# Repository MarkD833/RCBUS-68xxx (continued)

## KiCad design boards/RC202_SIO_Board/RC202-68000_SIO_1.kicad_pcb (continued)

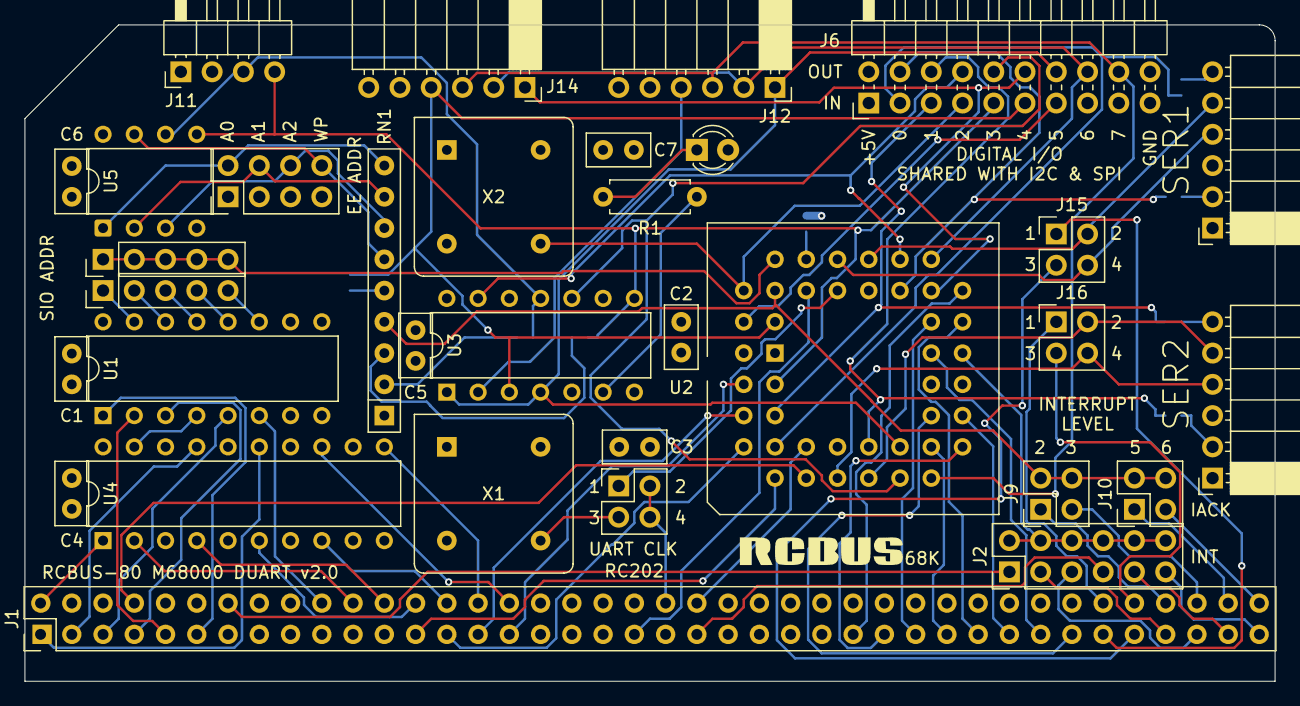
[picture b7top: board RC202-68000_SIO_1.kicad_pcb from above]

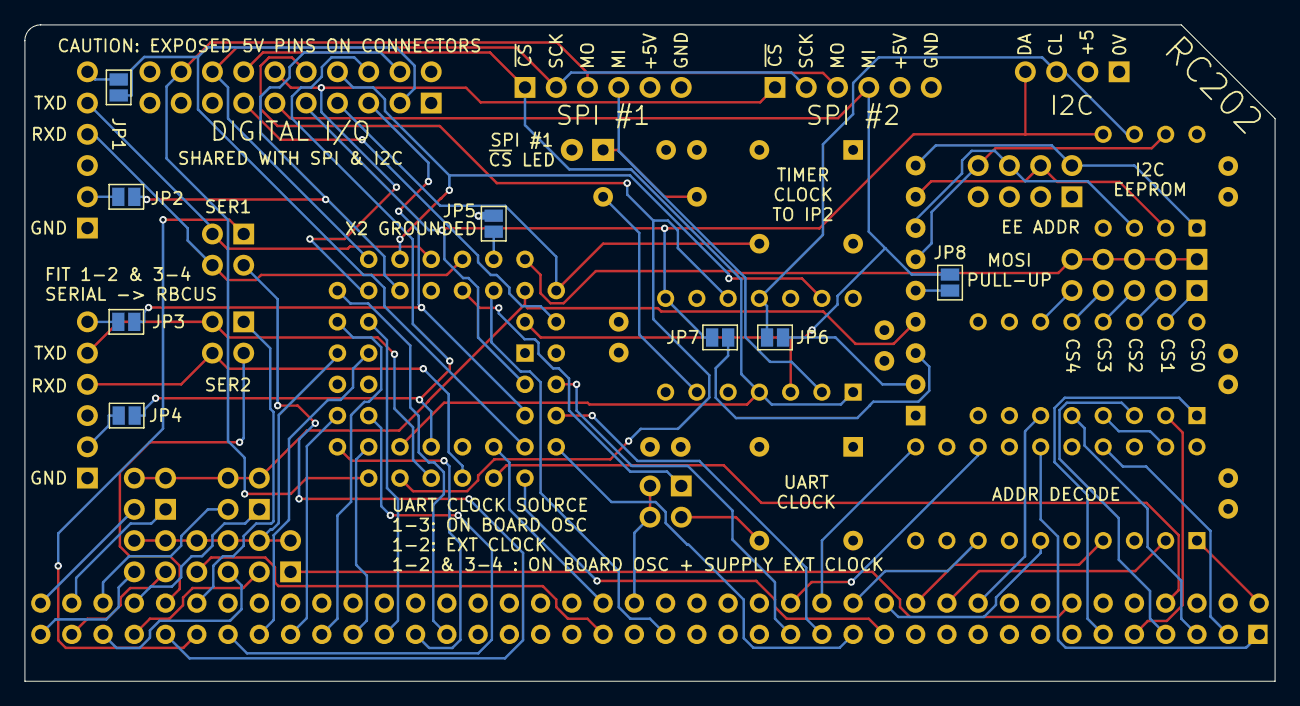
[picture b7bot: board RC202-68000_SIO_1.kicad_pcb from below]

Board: 4 copper layers, 101.6 x 53.3 mm, 41 parts (8 on the bottom side), 91 nets.

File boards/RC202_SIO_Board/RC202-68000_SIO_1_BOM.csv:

Reference,Value,Qty,Description
"C1,C2,C3,C4,C5,C6,C7",100n,7,Unpolarized ceramic capacitor
D1,LED,1,Light emitting diode
J1,RCBus_80PIN_68000,1,"Generic connector, double row, 02x40, right angle"
J2,Conn_02x06_Odd_Even,1,"Generic connector, double row, 02x06"
"J3,J4,J12,J14",Conn_01x06,4,"Generic connector, single row, 01x06, right angle"
"J5,J9,J10,J15,J16",Conn_02x02_Odd_Even,5,"Generic connector, double row, 02x02"
J6,Conn_02x10_Odd_Even,1,"Generic connector, double row, 02x10"
"J7,J8",Conn_01x05,2,"Generic connector, single row, 01x05"
J11,Conn_01x04,1,"Generic connector, single row, 01x04"
J13,Conn_02x04_Odd_Even,1,"Generic connector, double row, 02x04"
"JP1,JP2,JP3,JP4,JP6,JP7,JP8",SolderJumper,7,"Solder Jumper, 2-pole, open"
R1,1K,1,Resistor
RN1,4K7,1,"8 resistor network, star topology, bussed resistors, small symbol"
U1,74LS138,1,Decoder 3 to 8 active low outputs
U2,SCC68692C1A44,1,DUART + 8 Outputs & 6 Inputs
U3,74LS125,1,Quad buffer 3-State outputs
U4,74LS688,1,8-bit magnitude comparator
U5,24LC128,1,"I2C Serial EEPROM, 128Kb, DIP-8"
X1,3.6864MHz,1,"Crystal Clock Oscillator, DIP8-style metal package"
X2,1.0MHz,1,"Crystal Clock Oscillator, DIP8-style metal package"

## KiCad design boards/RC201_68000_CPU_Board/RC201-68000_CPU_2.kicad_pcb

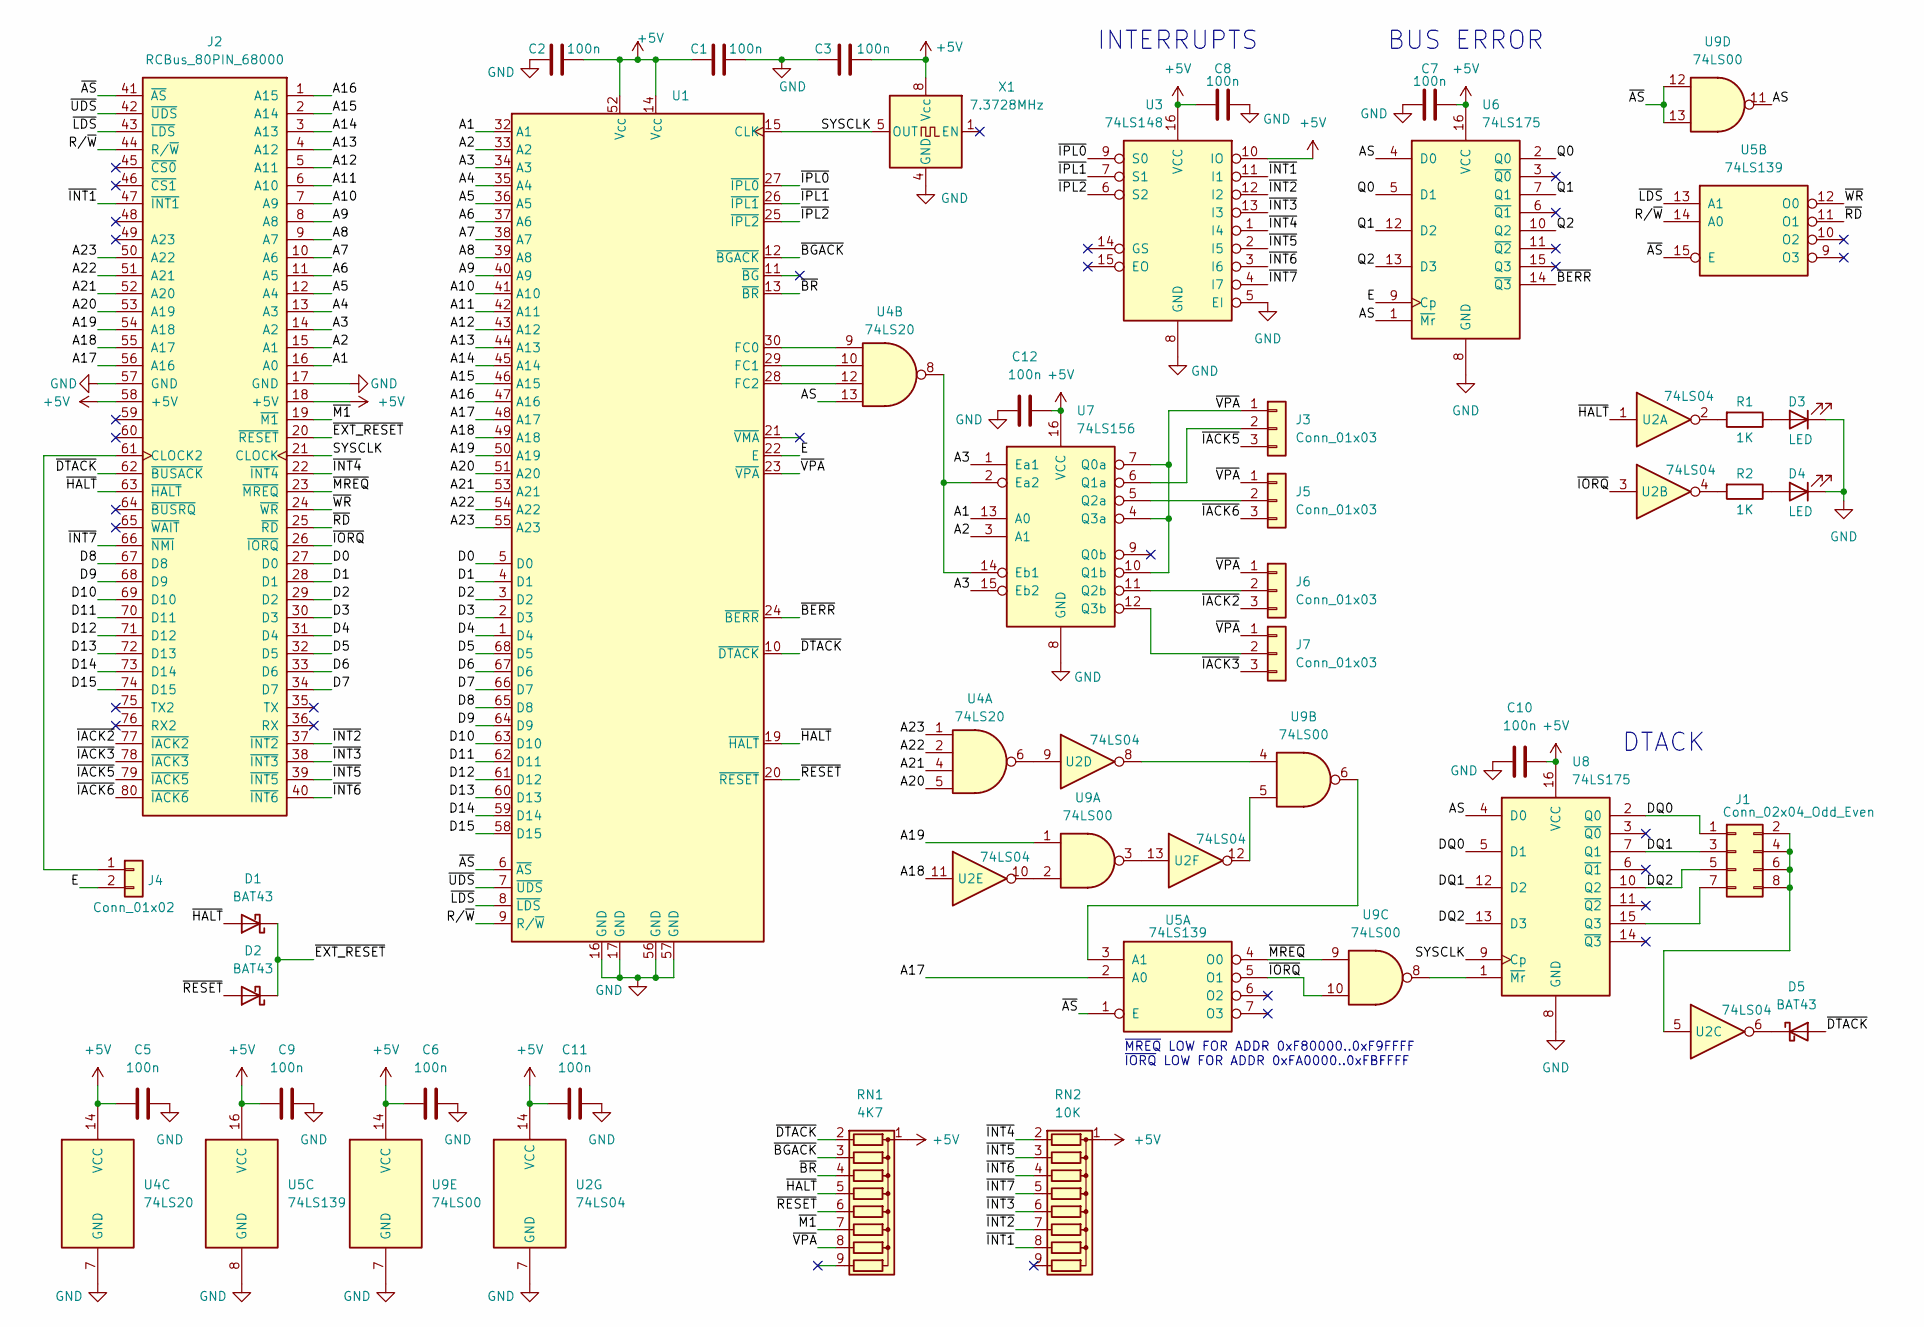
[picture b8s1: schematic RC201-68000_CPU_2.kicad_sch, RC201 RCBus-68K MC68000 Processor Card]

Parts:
C1, C2, C3, C5, C6, C7, C8, C9, C10, C11, C12: 100n; C_Disc_D5.0mm_W2.5mm_P2.50mm
D1, D2, D5: BAT43; D_DO-35_SOD27_P7.62mm_Horizontal
D3, D4: LED; LED_D3.0mm
J1: Conn_02x04_Odd_Even; PinHeader_2x04_P2.54mm_Vertical
J2: RCBus_80PIN_68000; RCBus_80p_Medium
J3, J5, J6, J7: Conn_01x03; PinHeader_1x03_P2.54mm_Vertical
J4: Conn_01x02; PinHeader_1x02_P2.54mm_Vertical
R1, R2: 1K; R_Axial_DIN0207_L6.3mm_D2.5mm_P7.62mm_Horizontal
RN1: 4K7; R_Array_SIP9
RN2: 10K; R_Array_SIP9
U1: PLCC-68_THT-Socket
U2: 74LS04; DIP-14_W7.62mm
U3: 74LS148; DIP-16_W7.62mm
U4: 74LS20; DIP-14_W7.62mm
U5: 74LS139; DIP-16_W7.62mm
U6, U8: 74LS175; DIP-16_W7.62mm
U7: 74LS156; DIP-16_W7.62mm
U9: 74LS00; DIP-14_W7.62mm
X1: 7.3728MHz; Oscillator_DIP-8

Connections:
+5V: C1.1, C2.2, C3.2, C5.1, C6.1, C7.2, C8.1, C9.1, C10.2, C11.1, C12.2, J2.18 (+5V), J2.58 (+5V), RN1.1 (common), RN2.1 (common), U1.14 (V_{CC}), U1.52 (V_{CC}), U2.14 (VCC), U3.10 (IO), U3.16 (VCC), U4.14 (VCC), U5.16 (VCC), U6.16 (VCC), U7.16 (VCC), U8.16 (VCC), U9.14 (VCC), X1.8 (Vcc)
/A1: J2.16 (A0), U1.32 (A1), U7.13 (A0)
/A2: J2.15 (A1), U1.33 (A2), U7.3 (A1)
/A3: J2.14 (A2), U1.34 (A3), U7.1 (Ea1), U7.15 (Eb2)
/A4: J2.13 (A3), U1.35 (A4)
/A5: J2.12 (A4), U1.36 (A5)
/A6: J2.11 (A5), U1.37 (A6)
/A7: J2.10 (A6), U1.38 (A7)
/A8: J2.9 (A7), U1.39 (A8)
/A9: J2.8 (A8), U1.40 (A9)
/A10: J2.7 (A9), U1.41 (A10)
/A11: J2.6 (A10), U1.42 (A11)
/A12: J2.5 (A11), U1.43 (A12)
/A13: J2.4 (A12), U1.44 (A13)
/A14: J2.3 (A13), U1.45 (A14)
/A15: J2.2 (A14), U1.46 (A15)
/A16: J2.1 (A15), U1.47 (A16)
/A17: J2.56 (A16), U1.48 (A17), U5.2 (A0)
/A18: J2.55 (A17), U1.49 (A18), U2.11
/A19: J2.54 (A18), U1.50 (A19), U9.1
/A20: J2.53 (A19), U1.51 (A20), U4.5
/A21: J2.52 (A20), U1.53 (A21), U4.4
/A22: J2.51 (A21), U1.54 (A22), U4.2
/A23: J2.50 (A22), U1.55 (A23), U4.1
/AS: U4.13, U6.1 (~Mr), U6.4 (D0), U8.4 (D0), U9.11
/D0: J2.27 (D0), U1.5 (D0)
/D1: J2.28 (D1), U1.4 (D1)
/D2: J2.29 (D2), U1.3 (D2)
/D3: J2.30 (D3), U1.2 (D3)
/D4: J2.31 (D4), U1.1 (D4)
/D5: J2.32 (D5), U1.68 (D5)
/D6: J2.33 (D6), U1.67 (D6)
/D7: J2.34 (D7), U1.66 (D7)
/D8: J2.67 (D8), U1.65 (D8)
/D9: J2.68 (D9), U1.64 (D9)
/D10: J2.69 (D10), U1.63 (D10)
/D11: J2.70 (D11), U1.62 (D11)
/D12: J2.71 (D12), U1.61 (D12)
/D13: J2.72 (D13), U1.60 (D13)
/D14: J2.73 (D14), U1.59 (D14)
/D15: J2.74 (D15), U1.58 (D15)
/DQ0: J1.1, U8.2 (Q0), U8.5 (D1)
/DQ1: J1.3, U8.7 (Q1), U8.12 (D2)
/DQ2: J1.5, U8.10 (Q2), U8.13 (D3)
/E: J4.2, U1.22 (E), U6.9 (Cp)
/Q0: U6.2 (Q0), U6.5 (D1)
/Q1: U6.7 (Q1), U6.12 (D2)
/Q2: U6.10 (Q2), U6.13 (D3)
/R/~W: J2.44 (R/~W), U1.9 (R/~W), U5.14 (A0)
/SYSCLK: J2.21 (CLOCK), U1.15 (CLK), U8.9 (Cp), X1.5 (OUT)
/~AS: J2.41 (~AS), U1.6 (~AS), U5.1 (E), U5.15 (E), U9.12, U9.13
/~BERR: U1.24 (~BERR), U6.14 (~Q3)
/~BGACK: RN1.3 (R2), U1.12 (~BGACK)
/~BR: RN1.4 (R3), U1.13 (~BR)
/~DTACK: D5.2 (A), J2.62 (~BUSACK), RN1.2 (R1), U1.10 (~DTACK)
/~EXT_RESET: D1.1 (K), D2.1 (K), J2.20 (~RESET)
/~HALT: D1.2 (A), J2.63 (~HALT), RN1.5 (R4), U1.19 (~HALT), U2.1
/~IACK2: J2.77 (~IACK2), J6.3
/~IACK3: J2.78 (~IACK3), J7.3
/~IACK5: J2.79 (~IACK5), J3.3
/~IACK6: J2.80 (~IACK6), J5.3
/~INT1: J2.47 (~INT1), RN2.8 (R7), U3.11 (I1)
/~INT2: J2.37 (~INT2), RN2.7 (R6), U3.12 (I2)
/~INT3: J2.38 (~INT3), RN2.6 (R5), U3.13 (I3)
/~INT4: J2.22 (~INT4), RN2.2 (R1), U3.1 (I4)
/~INT5: J2.39 (~INT5), RN2.3 (R2), U3.2 (I5)
/~INT6: J2.40 (~INT6), RN2.4 (R3), U3.3 (I6)
/~INT7: J2.66 (~NMI), RN2.5 (R4), U3.4 (I7)
/~IORQ: J2.26 (~IORQ), U2.3, U5.5 (O1), U9.10
/~IPL0: U1.27 (~IPL0), U3.9 (S0)
/~IPL1: U1.26 (~IPL1), U3.7 (S1)
/~IPL2: U1.25 (~IPL2), U3.6 (S2)
/~LDS: J2.43 (~LDS), U1.8 (~LDS), U5.13 (A1)
/~M1: J2.19 (~M1), RN1.7 (R6)
/~MREQ: J2.23 (~MREQ), U5.4 (O0), U9.9
/~RD: J2.25 (~RD), U5.11 (O1)
/~RESET: D2.2 (A), RN1.6 (R5), U1.20 (~RESET)
/~UDS: J2.42 (~UDS), U1.7 (~UDS)
/~VPA: J3.1, J5.1, J6.1, J7.1, RN1.8 (R7), U1.23 (~VPA), U7.4 (Q3a), U7.7 (Q0a), U7.10 (Q1b)
/~WR: J2.24 (~WR), U5.12 (O0)
GND: C1.2, C2.1, C3.1, C5.2, C6.2, C7.1, C8.2, C9.2, C10.1, C11.2, C12.1, D3.1 (K), D4.1 (K), J2.17 (GND), J2.57 (GND), U1.16 (GND), U1.17 (GND), U1.56 (GND), U1.57 (GND), U2.7 (GND), U3.5 (EI), U3.8 (GND), U4.7 (GND), U5.8 (GND), U6.8 (GND), U7.8 (GND), U8.8 (GND), U9.7 (GND), X1.4 (GND)
unnamed: D3.2 (A), R1.1
unnamed: D4.2 (A), R2.1
unnamed: D5.1 (K), U2.6
unnamed: J1.2, J1.4, J1.6, J1.8, U2.5
unnamed: J1.7, U8.15 (Q3)
unnamed: J2.61 (CLOCK2), J4.1
unnamed: J3.2, U7.6 (Q1a)
unnamed: J5.2, U7.5 (Q2a)
unnamed: J6.2, U7.11 (Q2b)
unnamed: J7.2, U7.12 (Q3b)
unnamed: R1.2, U2.2
unnamed: R2.2, U2.4
unnamed: U1.30 (FC0), U4.9
unnamed: U1.29 (FC1), U4.10
unnamed: U1.28 (FC2), U4.12
unnamed: U2.8, U9.4
unnamed: U2.9, U4.6
unnamed: U2.10, U9.2
unnamed: U2.12, U9.5
unnamed: U2.13, U9.3
unnamed: U5.3 (A1), U9.6
unnamed: U4.8, U7.2 (Ea2), U7.14 (Eb1)
unnamed: U8.1 (~Mr), U9.8

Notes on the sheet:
INTERRUPTS
DTACK
~{MREQ} LOW FOR ADDR 0xF80000..0xF9FFFF ~{IORQ} LOW FOR ADDR 0xFA0000..0xFBFFFF
BUS ERROR

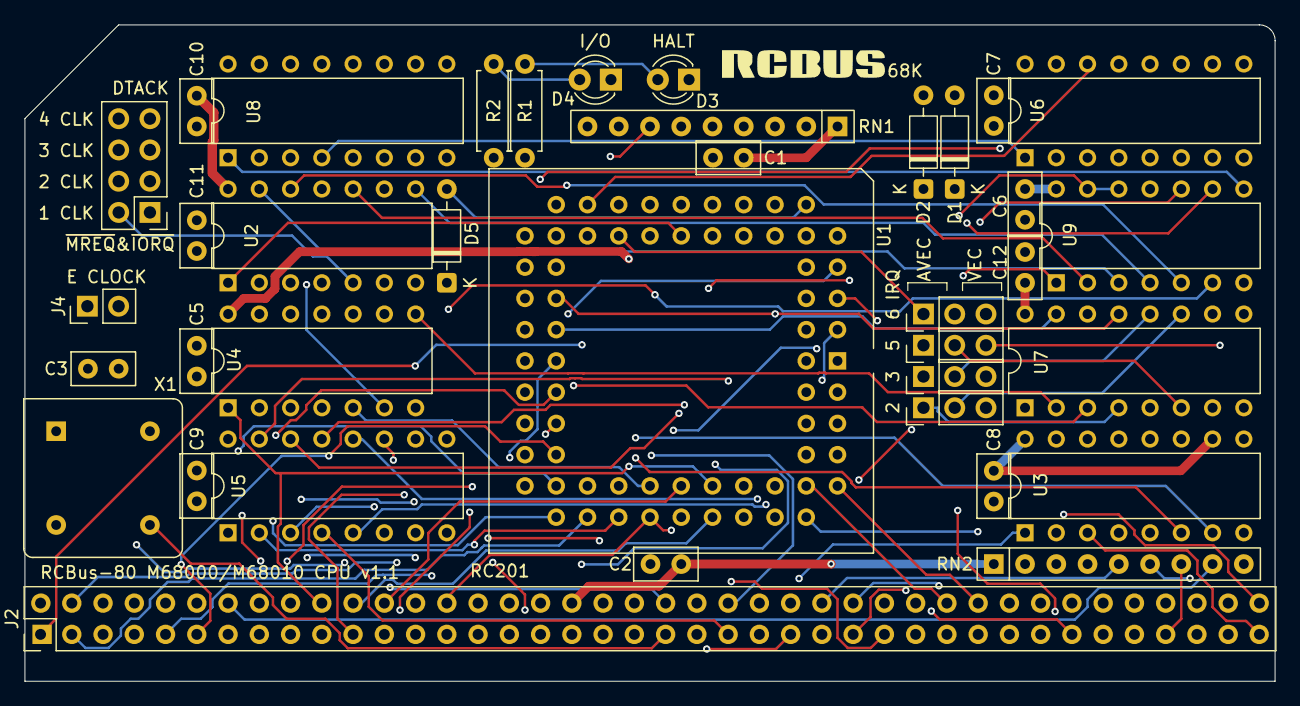
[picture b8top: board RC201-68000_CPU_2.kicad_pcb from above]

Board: 4 copper layers, 101.6 x 53.3 mm, 37 parts (0 on the bottom side), 104 nets.

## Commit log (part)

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2025-02-16 added board images
2025-02-16 extension issues
2025-02-24 Added PCB files etc
2025-02-24 Oops
2025-03-04 Updated progress
2025-03-05 Added new boards
2025-03-08 added monitor and code samples
2025-03-08 updated code readme
2025-03-08 updated SC129 text
2025-03-08 fixed link error
2025-03-10 added SC704 test code
2025-03-10 added SC705 code
2025-03-10 minor text update
2025-04-25 introduce CP/M68K v1.3
2025-04-25 corrected diskdefs
2025-05-04 Lots of updates
2025-05-04 Forgot to mention EhBASIC
2025-05-10 Update to v2 board set
    Lots of updates to reflect the new v2 boards that use the full RCBus 80 pins as well as slight modifications to the various test programs to reflect the new IO and MEM space addresses.
2025-05-10 Broken link to images
2025-05-12 Added details of SC611
2025-05-16 updated readme's
2025-05-24 software
    renamed the assembler code directory and added in the c code directory
2025-05-25 update C demo code
2025-05-25 Create LICENSE
2025-06-05 Added TMS9918A updates
2025-06-07 update demo code
    Tidy up the ASCII demo and introduce the Nyan Cat bitmap animation demo.
2025-06-20 Updated TMS9918A demos
    Demo updates and addition of the sprite demo.
2025-06-20 Update README.md
    Added sprites demo text.
2025-07-03 Added C code of ASCII demo
2025-07-03 typo
2025-07-04 updated setup instructions
2025-07-07 Added sprites C demo
2025-07-07 Added Nyan cat demo
2025-07-10 Added fern demo code
2025-07-11 Reorganised documentation
    Reorganised documentation and added comments in TMS library.
2025-07-11 update image links
2025-08-05 added MC68901 demo code
2025-08-05 added MFP serial echo
2025-08-05 minor updates
2025-08-14 added MC68302
2025-08-15 more 68302 details
2025-08-21 add new rom/ram board
2025-08-22 Update to readme
2025-08-22 update parts list
2025-08-22 Updated pinout list and boards readme
2025-08-22 added note re clock on 68230
2025-08-23 added 68230 PI/T information
2025-09-13 update to PIO board and 68302 board notes
2025-10-05 Reformat readme
2025-10-26 Added BOMs for each board
2025-10-29 Updated board readme files.
2025-11-01 Updated BOMs and added gerber files for all boards.
2025-11-01 68000 clock
    Added details of the 68000 board clock frequencies used.
2025-11-06 Added V9958A demonstrations
    Based around Dean Netherton's HDMI for RC board.
2025-11-06 minor corrections
2025-11-19 Corrections to RCBus pinout
    Corrected nDTACK pin.
    Deleted nINT3.
    Moved nINT2 to pin 38.
2025-11-29 Added 68302 ROM monitor code
2025-12-07 Changed readme from plain test to Markdown
2025-12-07 Add comment to 68000 CPU about CPU Orientation
2025-12-07 Convert Serial card Readme from plain text to Markdown
2025-12-07 Added some jumper settting details to the serial card Readme
2025-12-07 Change Serial readme from plain text to Markdown
2025-12-07 Corrections to missing tracks
2025-12-07 Add some jumper settings to serial Readme
2025-12-07 Converted PIO readme to Markdown
2025-12-07 Convert MFP Readme to Markdown
2025-12-07 Convered ROM_RAM_2 board Readme to Markdown
2025-12-08 Updated some board readme's
2025-12-08 Updated board readme's
2025-12-09 updated rom/ram board #2 schematic notes
2025-12-09 update readme's and added s-record file
    68302 readme updated
    s-rec file containing MON68Kv1.3, CP/M, CP/M BIOS and EhBASIC.
2025-12-09 updated 68302 readme
2025-12-10 updated 68000 board readme
2025-12-12 update readme's
2025-12-12 updated various readme's
2025-12-14 Annotated schematic with notes on errors found so far.
2025-12-14 added SPI master board
2025-12-14 Updated schematics
2025-12-14 spelling errors
2025-12-16 updated readme's and added LBE board
2025-12-26 Extended baud rate details for the Philips devices.
2025-12-26 Added LBE board details etc
2025-12-27 Change method of monitor variable definitions
    With some assemblers (e.g. Vasm) the previous method of using "ORG xxxx" and
    <var> ds.b <N>
    forces the assembler to fill the blank between the end of the code and the ORG
    statement
    Changing the definitions to be just "EQU"s doesn't force the aseembler to
    fill in the blank.
2025-12-27 Remove spurious spaces after commas
    Some assemblers (e.g. vasm) don't like a space after a comma in mnemonics
    This commit removes spaces after commas in mnemonics only (i.e. not in comments!)
2025-12-27 Changed PC-relative assembly syntax to modern Motorola style.
    The code was written in an older style of:
    lea bemsg1(PC),a0
    to:
    lea (bemsg1,PC),A0
    which is accepted by more modern assemblers (e.g. vasm)
2025-12-27 Add conditional assembly for Vasm
    Easy68k and Vasm use different methods to ensure alignment. Easy68k uses:
    ORG (*+1)&-2
    Whereas Vasm uses:
    align 2
2026-01-07 Added note re 68681 X2 pin
2026-01-08 updated MON68K to support 115200 baud
2026-01-08 Added note re IRQ2 setting
2026-01-14 Update README.md
    Added note re issues with ehBasic running on v1.4 of rcMON68K.
2026-01-15 Corrected serial comms fault
2026-01-17 Added SIO & MATHS board
2026-01-18 updated readme with more board designs
2026-01-18 Updated address ranges for new boards
2026-01-25 Updated LBE board details
2026-02-12 Updated readme's for LBE #2
2026-02-15 Removed LBE #2
2026-02-16 Corrected spelling
2026-03-07 updated SPI board details
2026-03-07 corrected typo
2026-03-14 notes re series 2 boards
2026-03-14 can't spell!
2026-03-14 Added series 2 boards and images
2026-03-14 added more board details
2026-03-16 added details of 68302 ROM/RAM swap monitor
2026-03-17 corrected images
2026-03-28 Reorganise and rename boards
2026-03-28 updated RCBus pinout
2026-03-28 correction to command line
2026-04-08 reorganise c code folder
2026-04-08 added libc, libm, crt0 and SC611 demo
2026-04-08 added SC704 I2C scanner
2026-04-08 added SC704 read & write demo
2026-04-08 added TMS9918A ASCII chars demo
2026-04-08 Added TMS9918A demos
2026-04-08 Added V9958 demos
2026-04-08 Added V9958 demo
2026-06-15 updated rcMON68K
2026-06-15 added s-records
2026-06-15 spelling error(s)
2026-06-16 minor doc changes
